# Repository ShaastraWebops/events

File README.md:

Offline Events - ERP
======

An app for events to use for general ERP usage

### Setup
1. Copy the `settings.sample.py` to `settings.py`
 - Edit the proxy settings if you are in a proxy environment. If not, comment those lines.
2. Copy the `client_secret.sample.json` to `client_secret.json`
 - Use your own secret key for google app.

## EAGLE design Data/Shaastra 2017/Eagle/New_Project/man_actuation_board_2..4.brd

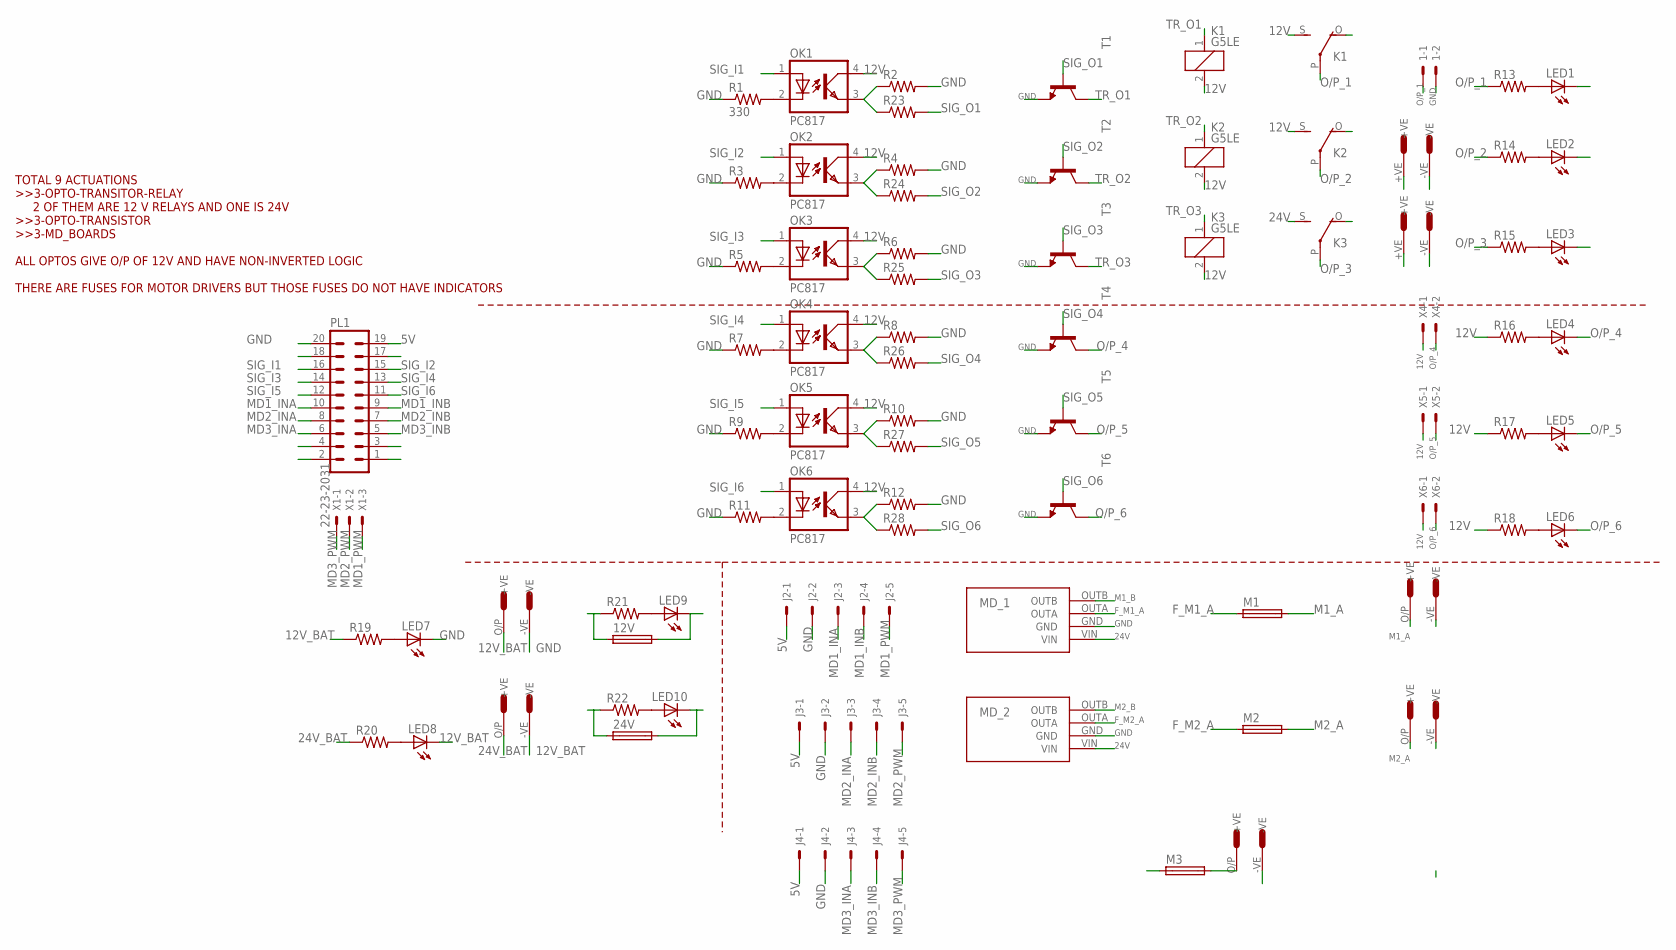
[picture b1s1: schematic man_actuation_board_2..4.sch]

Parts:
0-12_BAT, 12-24_I/P: MOLEX_4; MOLEX_2K14
1: 1; 22-23-2021
12V, 24V: SH25
J2, J3, J4: 22-27-2051-05; 6410-05
K1, K2, K3: G5LE
LED1, LED2, LED3, LED4, LED5, LED6, LED7, LED8, LED9, LED10: LED1206; LED-1206
M1, M2, M3: SH25
MD_1, MD_2: MOTOR_DRIVER
OK1, OK2, OK3, OK4, OK5, OK6: PC817; DIL04
PL1: ML20ML20; ML20
R1: 330; 1206
R2, R3, R4, R5, R6, R7, R8, R9, R10, R11, R12, R13, R14, R15, R16, R17, R18, R19, R20, R21, R22, R23, R24, R25, R26, R27, R28: RESISTOR1206; 1206
T1, T2, T3, T4, T5, T6: -NPN-TO5; TO5
U$1, U$2, U$3: MOLEX_4; MOLEX_2K14
U$4, U$5: MOLEXM; MOLEX_2K13
X1: 22-23-2031
X4: 4; 22-23-2021
X5: 5; 22-23-2021
X6: 6; 22-23-2021

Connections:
5V: J2.1, J3.1, J4.1, PL1.19
12V: 12V.2, K1.2, K1.S, K2.2, K2.S, K3.2, LED9.C, OK1.4 (COL), OK2.4 (COL), OK3.4 (COL), OK4.4 (COL), OK5.4 (COL), OK6.4 (COL), R16.1, R17.1, R18.1, X4.1, X5.1, X6.1
12V_BAT: 0-12_BAT.O/P (+VE), 12-24_I/P.-VE, 12V.1, LED8.C, R19.1, R21.1
12V_M: M3.2, U$3.O/P (+VE)
24V: 24V.2, K3.S, LED10.C, M3.1, MD_1.VIN, MD_2.VIN
24V_BAT: 12-24_I/P.O/P (+VE), 24V.1, R20.1, R22.1
F_M1_A: M1.1, MD_1.OUTA
F_M2_A: M2.1, MD_2.OUTA
GND: 0-12_BAT.-VE, 1.2, J2.2, J3.2, J4.2, LED1.C, LED2.C, LED3.C, LED7.C, MD_1.GND, MD_2.GND, PL1.20, R1.1, R2.2, R3.1, R4.2, R5.1, R6.2, R7.1, R8.2, R9.1, R10.2, R11.1, R12.2, T1.1 (E), T2.1 (E), T3.1 (E), T4.1 (E), T5.1 (E), T6.1 (E), U$3.-VE, U$4.-VE, U$5.-VE
M1_A: M1.2, U$1.O/P (+VE)
M1_B: MD_1.OUTB, U$1.-VE
M2_A: M2.2, U$2.O/P (+VE)
M2_B: MD_2.OUTB, U$2.-VE
MD1_INA: J2.3, PL1.10
MD1_INB: J2.4, PL1.9
MD1_PWM: J2.5, X1.3
MD2_INA: J3.3, PL1.8
MD2_INB: J3.4, PL1.7
MD2_PWM: J3.5, X1.2
MD3_INA: J4.3, PL1.6
MD3_INB: J4.4, PL1.5
MD3_PWM: J4.5, X1.1
unnamed: OK1.2 (C), R1.2
unnamed: LED1.A, R13.2
unnamed: LED2.A, R14.2
unnamed: OK2.2 (C), R3.2
unnamed: LED3.A, R15.2
unnamed: LED4.A, R16.2
unnamed: LED5.A, R17.2
unnamed: LED6.A, R18.2
unnamed: LED7.A, R19.2
unnamed: OK3.2 (C), R5.2
unnamed: LED8.A, R20.2
unnamed: OK4.2 (C), R7.2
unnamed: LED9.A, R21.2
unnamed: LED10.A, R22.2
unnamed: OK5.2 (C), R9.2
unnamed: OK1.3 (EMIT), R2.1, R23.1
unnamed: OK2.3 (EMIT), R4.1, R24.1
unnamed: OK3.3 (EMIT), R6.1, R25.1
unnamed: OK4.3 (EMIT), R8.1, R26.1
unnamed: OK5.3 (EMIT), R10.1, R27.1
unnamed: OK6.3 (EMIT), R12.1, R28.1
unnamed: OK6.2 (C), R11.2
O/P_1: 1.1, K1.P, R13.1
O/P_2: K2.P, R14.1, U$5.+VE
O/P_3: K3.P, R15.1, U$4.+VE
O/P_4: LED4.C, T4.3 (C), X4.2
O/P_5: LED5.C, T5.3 (C), X5.2
O/P_6: LED6.C, T6.3 (C), X6.2
SIG_I1: OK1.1 (A), PL1.16
SIG_I2: OK2.1 (A), PL1.15
SIG_I3: OK3.1 (A), PL1.14
SIG_I4: OK4.1 (A), PL1.13
SIG_I5: OK5.1 (A), PL1.12
SIG_I6: OK6.1 (A), PL1.11
SIG_O1: R23.2, T1.2 (B)
SIG_O2: R24.2, T2.2 (B)
SIG_O3: R25.2, T3.2 (B)
SIG_O4: R26.2, T4.2 (B)
SIG_O5: R27.2, T5.2 (B)
SIG_O6: R28.2, T6.2 (B)
TR_O1: K1.1, T1.3 (C)
TR_O2: K2.1, T2.3 (C)
TR_O3: K3.1, T3.3 (C)

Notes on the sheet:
TOTAL 9 ACTUATIONS >>3-OPTO-TRANSITOR-RELAY 2 OF THEM ARE 12 V RELAYS AND ONE IS 24V >>3-OPTO-TRANSISTOR >>3-MD_BOARDS ALL OPTOS GIVE O/P OF 12V AND HAVE NON-INVERTED LOGIC THERE ARE FUSES FOR MOTOR DRIVERS BUT THOSE FUSES DO NOT HAVE INDICATORS

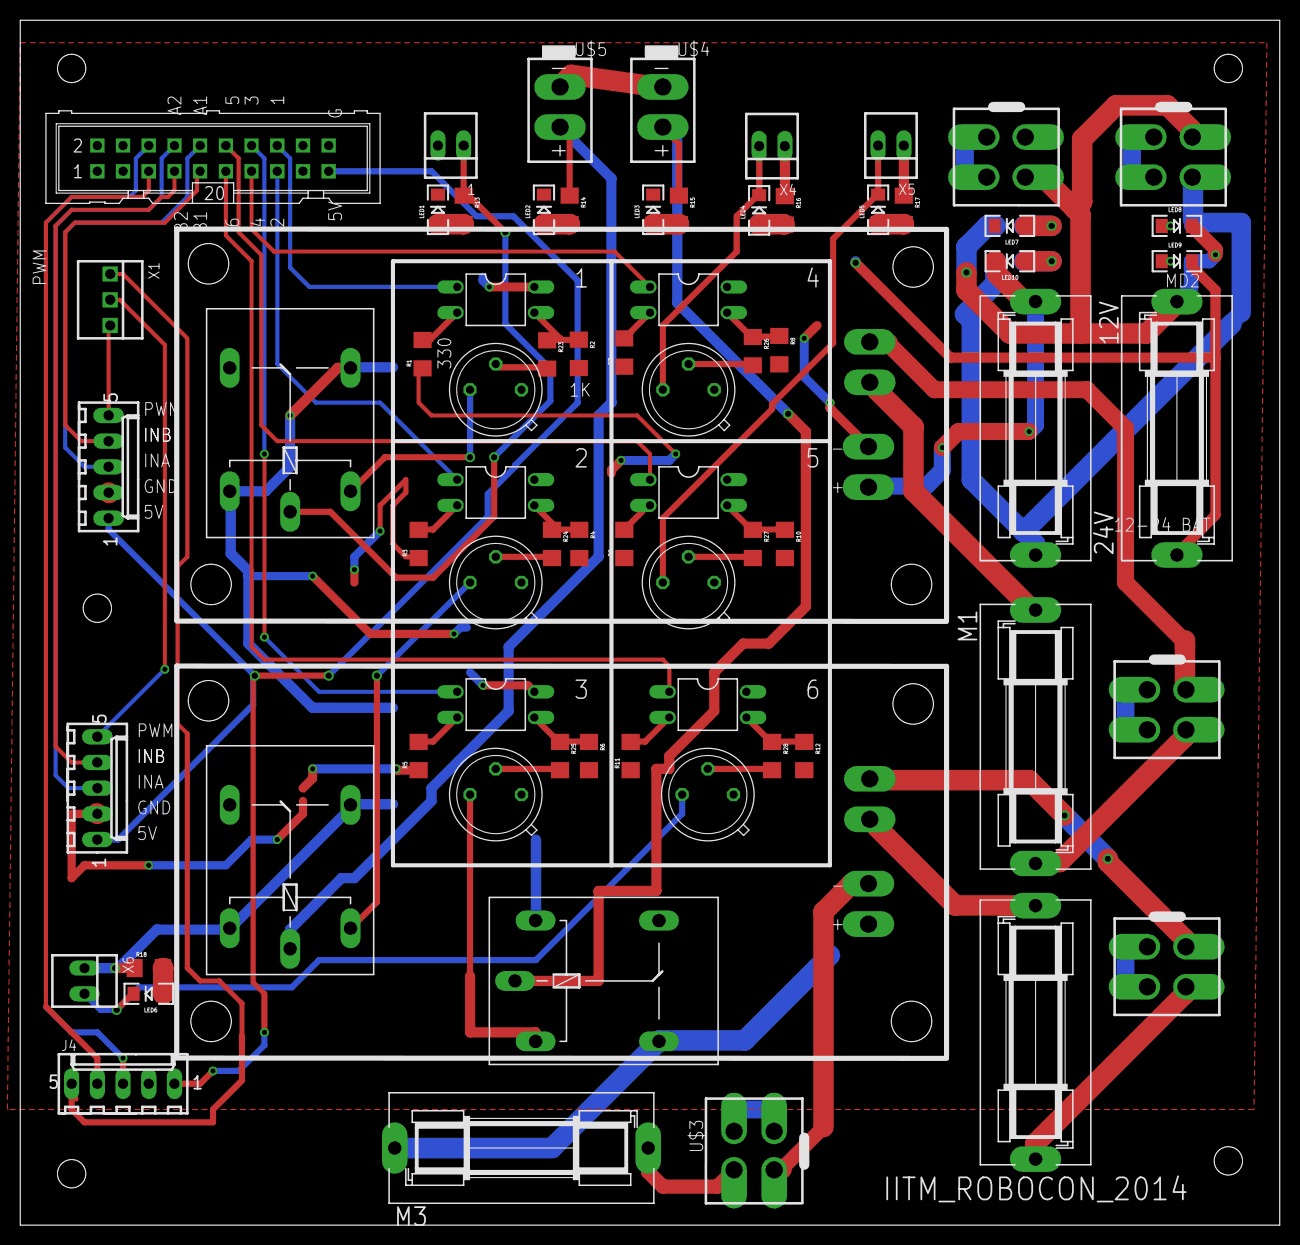
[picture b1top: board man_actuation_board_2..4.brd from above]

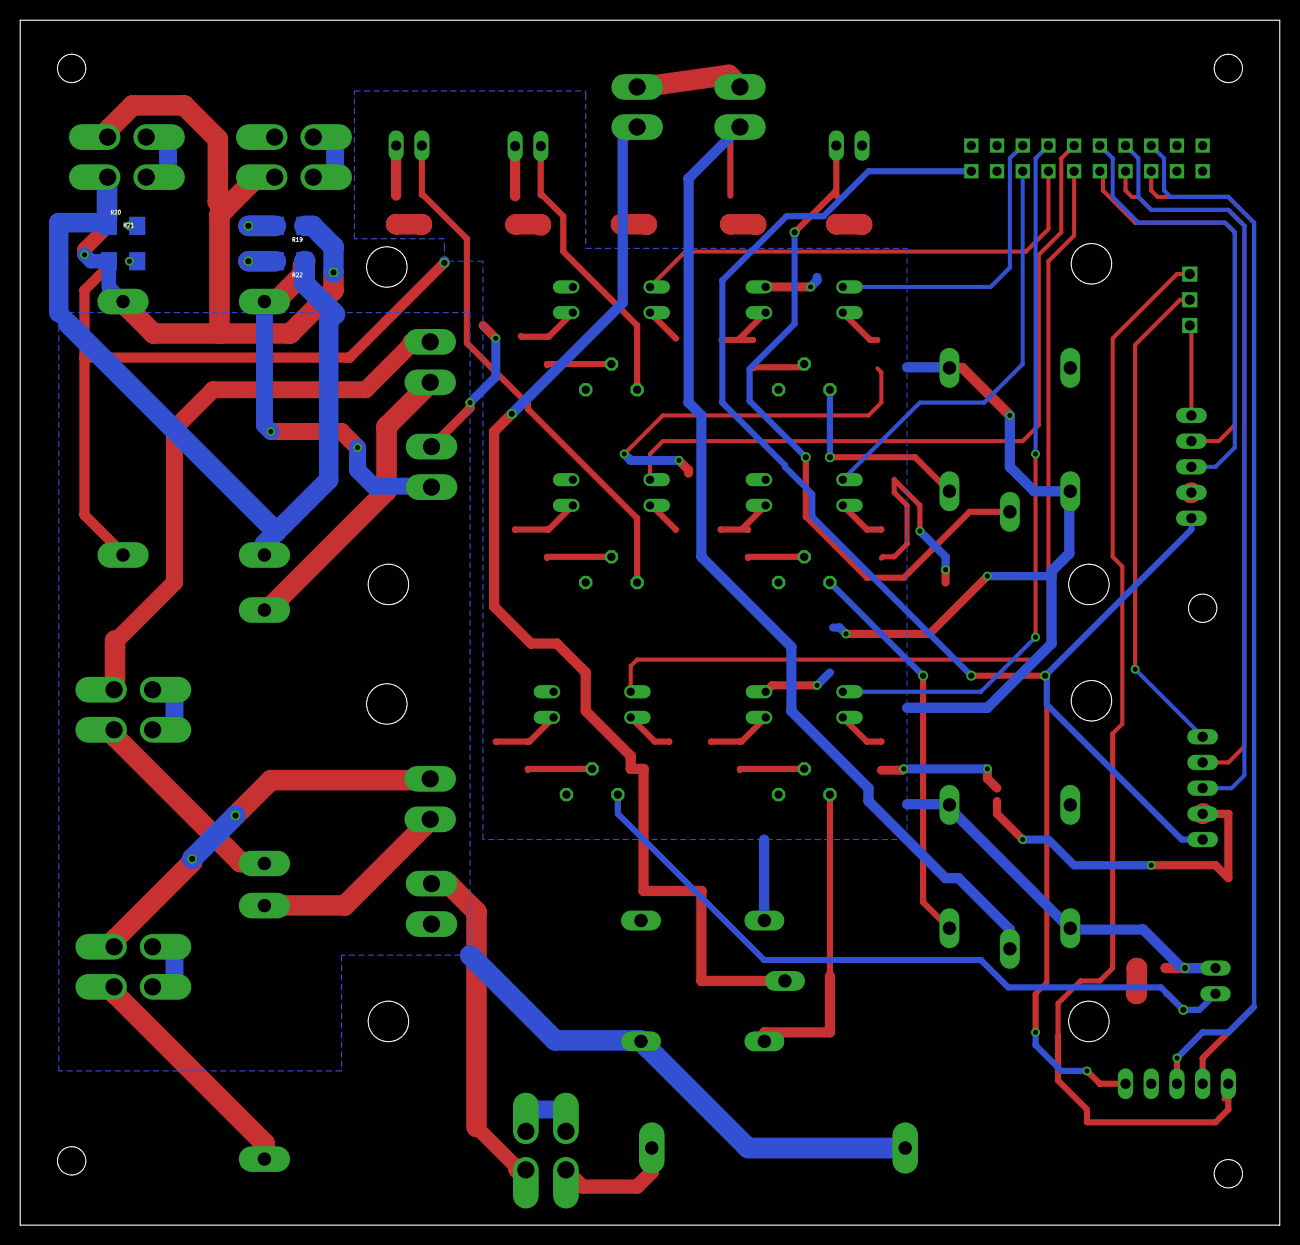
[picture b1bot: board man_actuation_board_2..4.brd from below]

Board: 2 copper layers, 124.5 x 119.1 mm, 76 parts (4 on the bottom side), 65 nets.

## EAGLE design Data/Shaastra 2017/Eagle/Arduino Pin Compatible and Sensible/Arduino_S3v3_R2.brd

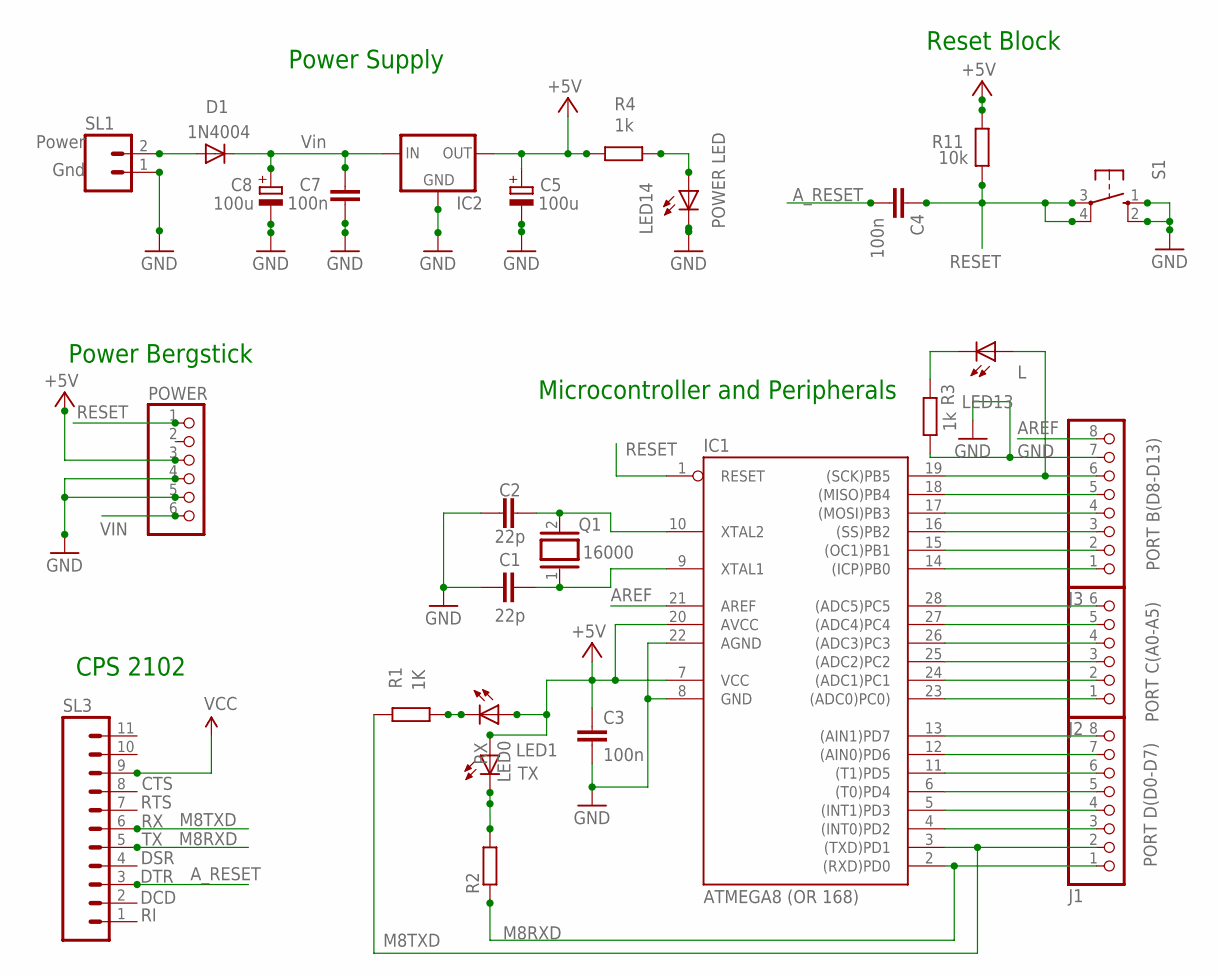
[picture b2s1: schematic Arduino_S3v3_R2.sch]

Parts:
C1, C2: 22p; C050-025X075
C3, C4, C7: 100n; C050-025X075
C5, C8: 100u; E3,5-8
D1: 1N4004; DO41-10
IC1: ATMEGA8 (OR 168); DIL28-3
IC2: 78XXL
J1: PORT D(D0-D7); 1X08
J2: PORT C(A0-A5); 1X06
J3: PORT B(D8-D13); 1X08
LED0: RX; LED3MM
LED1: TX; LED3MM
LED13: L; LED3MM
LED14: POWER LED; LED3MM
POWER: PINHD-1X6; 1X06
Q1: 16000; Q
R1: 1K; 0207/10
R2: R-EU_0207/10; 0207/10
R3, R4: 1k; 0207/10
R11: 10k; 0207/10
S1: 10-XX; B3F-10XX
SL1: M02; 02P
SL3: M11; 11P

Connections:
3V3: POWER.2
+5V: C3.1, C5.+, IC1.7 (VCC), IC1.20 (AVCC), IC2.OUT, LED0.A, LED1.A, POWER.3, R4.2, R11.2
AREF: IC1.21 (AREF), J3.8
AUTO_RESET: C4.2, SL3.3
GND: C1.1, C2.1, C3.2, C5.-, C7.1, C8.-, IC1.8 (GND), IC1.22 (AGND), IC2.GND, J3.7, LED14.K (C), POWER.4, POWER.5, R3.1, S1.1 (S), S1.2 (S1), SL1.1
M8RXD: IC1.2 ((RXD)PD0), J1.1, R2.1, SL3.5
M8TXD: IC1.3 ((TXD)PD1), J1.2, R1.2, SL3.6
unnamed: IC1.18 ((MISO)PB4), J3.5
unnamed: LED0.K (C), R1.1
unnamed: LED14.A, R4.1
unnamed: IC1.17 ((MOSI)PB3), J3.4
unnamed: IC1.14 ((ICP)PB0), J3.1
unnamed: C1.2, IC1.9 (XTAL1), Q1.1
unnamed: C2.2, IC1.10 (XTAL2), Q1.2
unnamed: LED1.K (C), R2.2
unnamed: IC1.4 ((INT0)PD2), J1.3
unnamed: IC1.5 ((INT1)PD3), J1.4
unnamed: IC1.6 ((T0)PD4), J1.5
unnamed: IC1.11 ((T1)PD5), J1.6
unnamed: IC1.12 ((AIN0)PD6), J1.7
unnamed: IC1.13 ((AIN1)PD7), J1.8
unnamed: IC1.23 ((ADC0)PC0)), J2.1
unnamed: IC1.24 ((ADC1)PC1), J2.2
unnamed: IC1.25 ((ADC2)PC2), J2.3
unnamed: IC1.26 ((ADC3)PC3), J2.4
unnamed: IC1.27 ((ADC4)PC4), J2.5
unnamed: IC1.28 ((ADC5)PC5), J2.6
unnamed: IC1.15 ((OC1)PB1), J3.2
unnamed: IC1.16 ((SS)PB2), J3.3
unnamed: LED13.K (C), R3.2
POWER: D1.A, SL1.2
RESET: C4.1, IC1.1 (RESET), POWER.1, R11.1, S1.3, S1.4 (P1)
SCK: IC1.19 ((SCK)PB5), J3.6, LED13.A
VCC: SL3.9
VIN: C7.2, C8.+, D1.C, IC2.IN, POWER.6

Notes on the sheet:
Vin
Gnd
Power Supply
Reset Block
Power Bergstick
CPS 2102
Microcontroller and Peripherals
CTS
RTS
DSR
DTR
DCD
A_RESET
Power

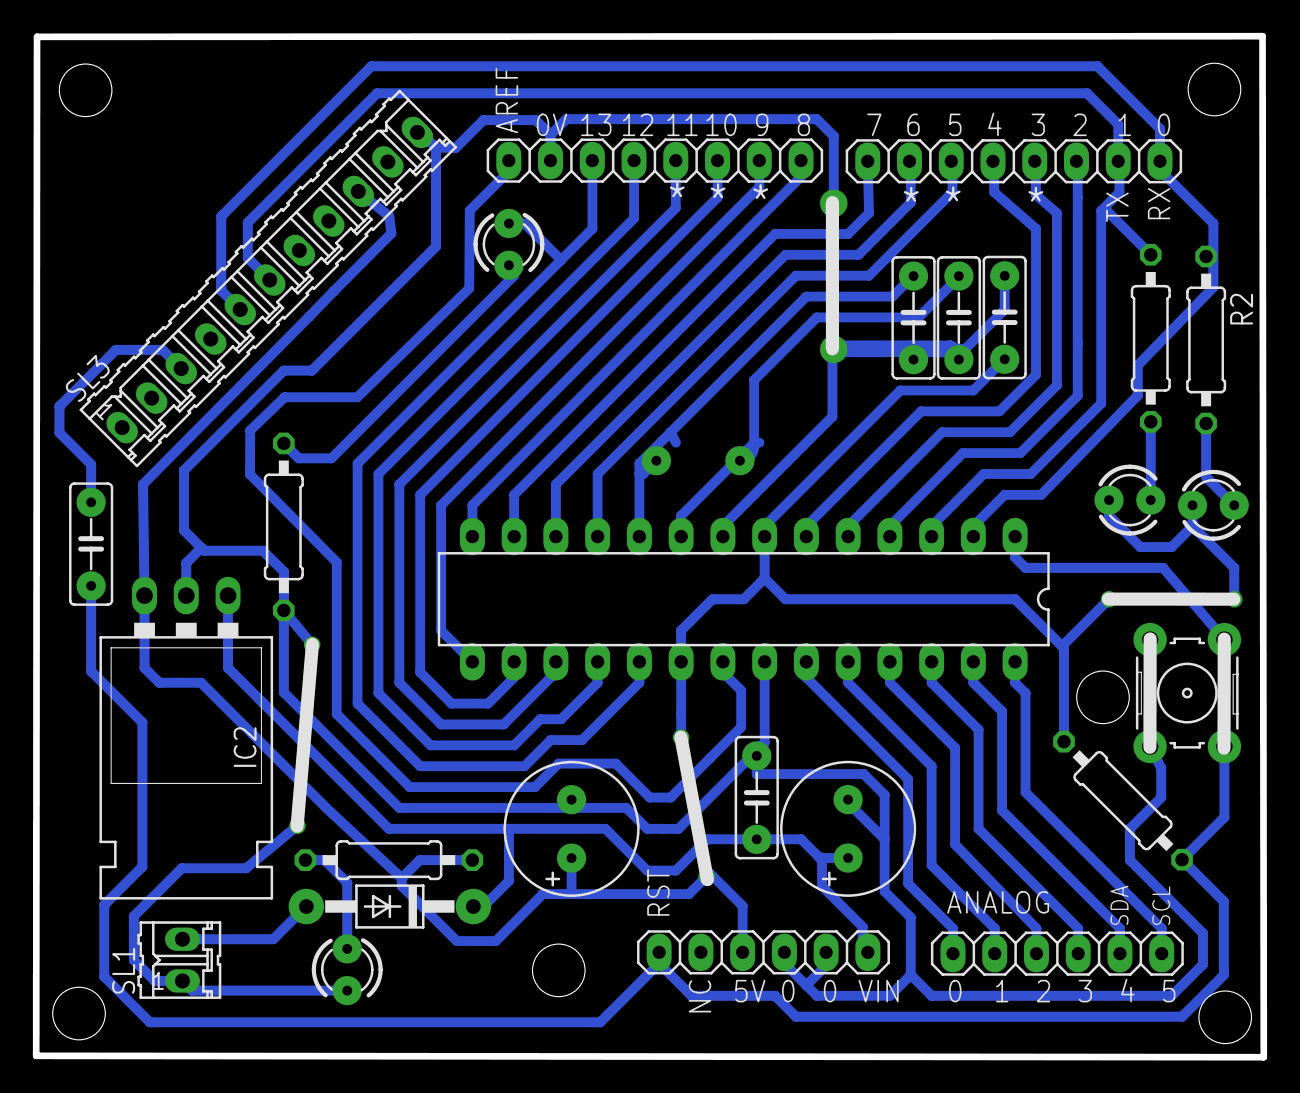
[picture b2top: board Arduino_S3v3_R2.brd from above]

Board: 2 copper layers, 74.7 x 62.1 mm, 27 parts (1 on the bottom side), 33 nets.

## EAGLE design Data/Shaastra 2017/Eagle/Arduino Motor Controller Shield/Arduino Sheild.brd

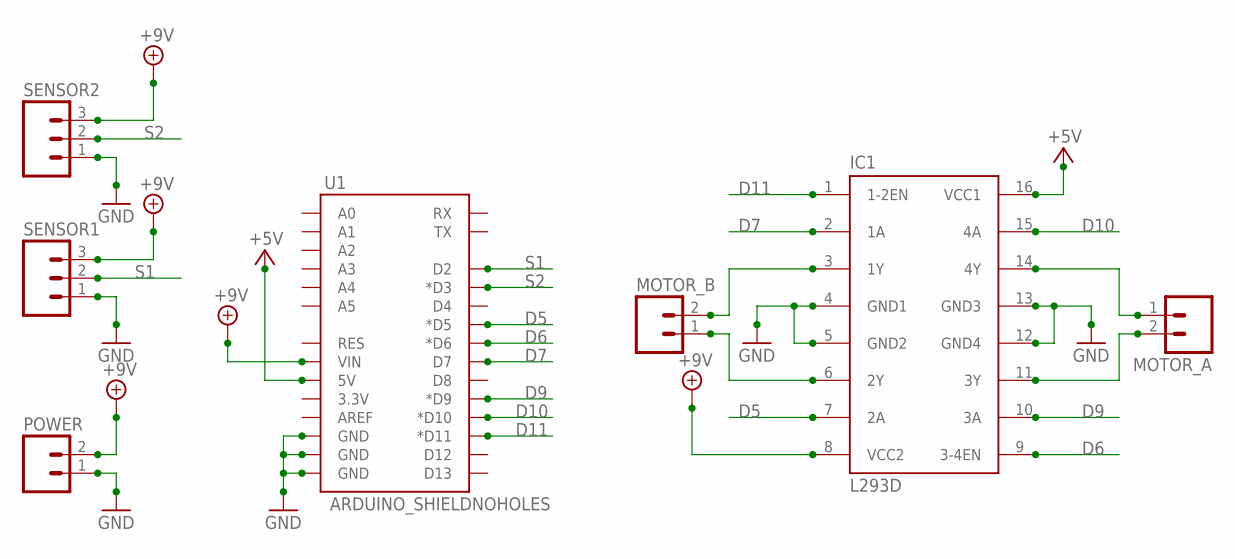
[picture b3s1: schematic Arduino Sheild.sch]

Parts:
IC1: L293D; DIL16
MOTOR_A: M02; 02P
MOTOR_B: M02; 02P
POWER: M02; 02P
SENSOR1, SENSOR2: M03; 03P
U1: ARDUINO_SHIELDNOHOLES; DUEMILANOVE_SHIELD_NOHOLES

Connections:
+5V: IC1.16 (VCC1), U1.5V
+9V: IC1.8 (VCC2), POWER.2, SENSOR1.3, SENSOR2.3, U1.VIN
D5: IC1.7 (2A), U1.D5 (*D5)
D6: IC1.9 (3-4EN), U1.D6 (*D6)
D7: IC1.2 (1A), U1.D7
D9: IC1.10 (3A), U1.D9 (*D9)
D10: IC1.15 (4A), U1.D10 (*D10)
D11: IC1.1 (1-2EN), U1.D11 (*D11)
GND: IC1.4 (GND1), IC1.5 (GND2), IC1.12 (GND4), IC1.13 (GND3), POWER.1, SENSOR1.1, SENSOR2.1, U1.GND@0 (GND), U1.GND@1 (GND), U1.GND@2 (GND)
unnamed: IC1.3 (1Y), MOTOR_B.2
unnamed: IC1.6 (2Y), MOTOR_B.1
unnamed: IC1.14 (4Y), MOTOR_A.1
unnamed: IC1.11 (3Y), MOTOR_A.2
S1: SENSOR1.2, U1.D2
S2: SENSOR2.2, U1.D3 (*D3)

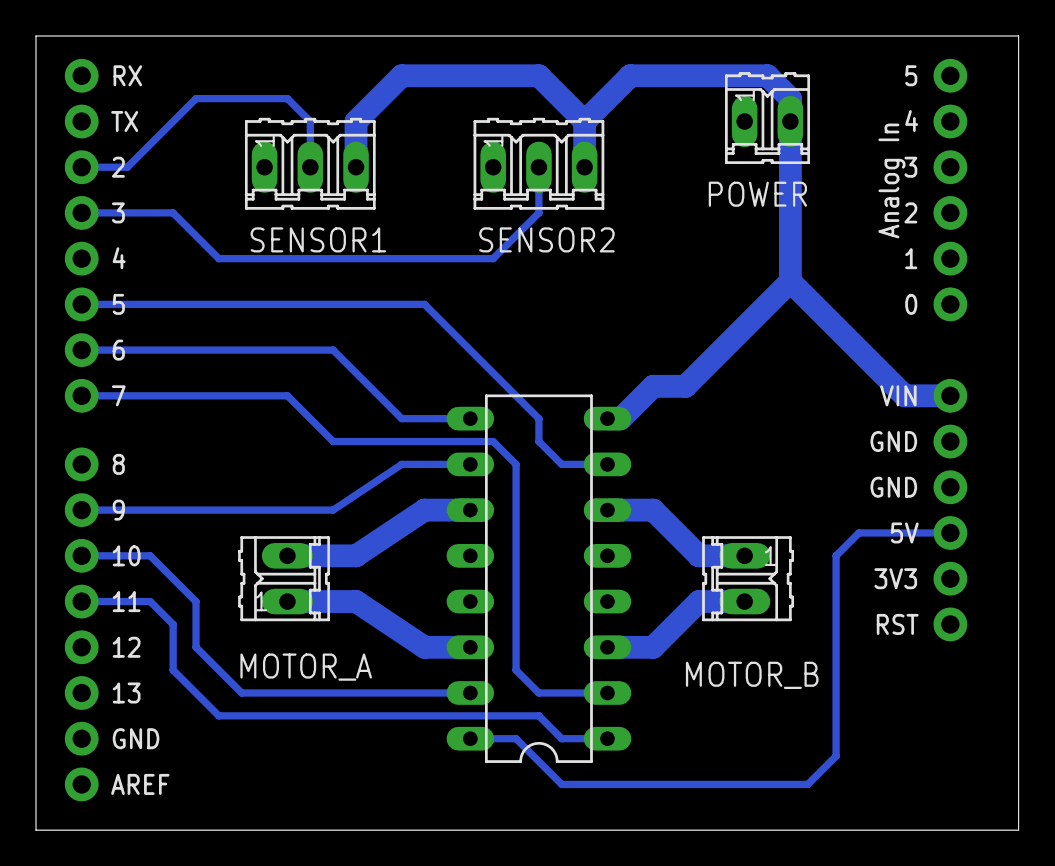
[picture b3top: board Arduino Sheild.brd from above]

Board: 2 copper layers, 54.6 x 44.1 mm, 7 parts (0 on the bottom side), 15 nets.

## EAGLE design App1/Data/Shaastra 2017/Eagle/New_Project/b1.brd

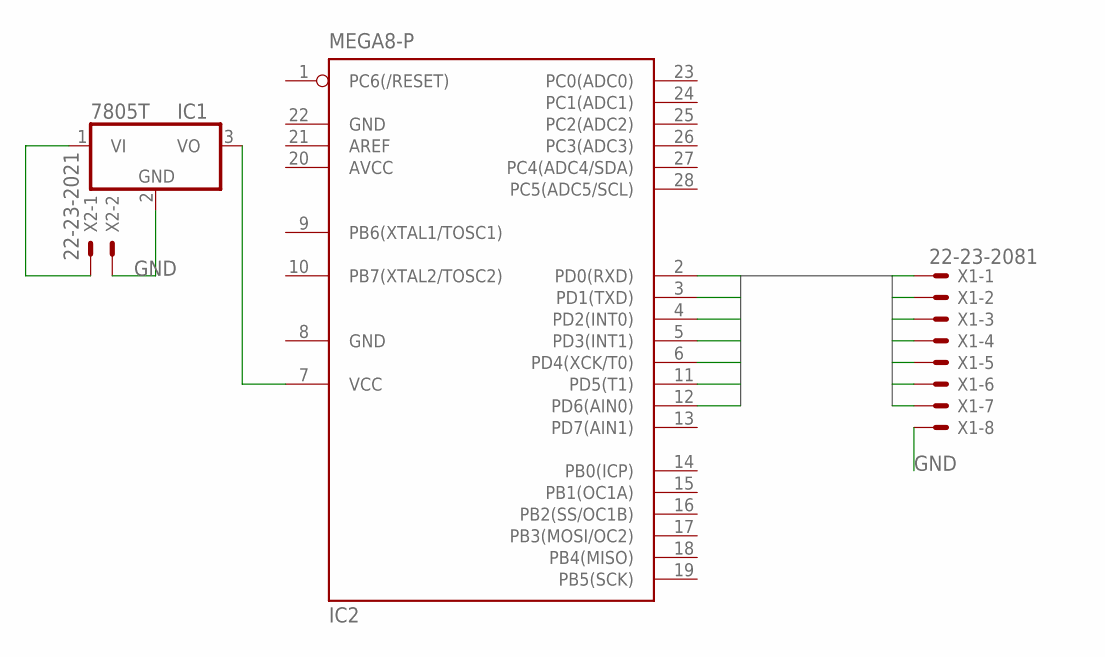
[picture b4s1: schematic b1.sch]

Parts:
IC1: 7805T; TO220H
IC2: MEGA8-P; DIL28-3
X1: 22-23-2081
X2: 22-23-2021

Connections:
AVCC: IC2.20 (AVCC)
GND: IC1.2 (GND), IC2.8 (GND), IC2.22 (GND), X1.8, X2.2
unnamed: IC1.1 (VI), X2.1
unnamed: IC1.3 (VO), IC2.7 (VCC)
P1: IC2.2 (PD0(RXD)), X1.1
P2: IC2.3 (PD1(TXD)), X1.2
P3: IC2.4 (PD2(INT0)), X1.3
P4: IC2.5 (PD3(INT1)), X1.4
P5: IC2.6 (PD4(XCK/T0)), X1.5
P6: IC2.11 (PD5(T1)), X1.6
P7: IC2.12 (PD6(AIN0)), X1.7

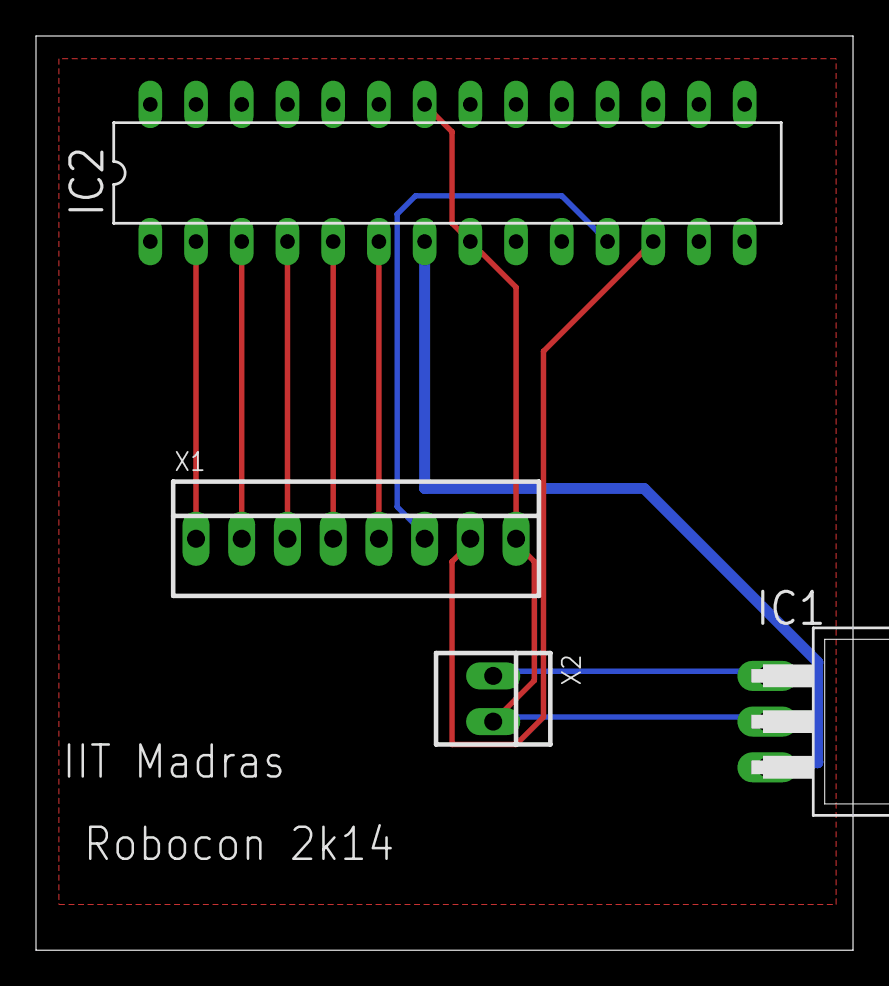
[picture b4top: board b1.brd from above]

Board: 2 copper layers, 45.4 x 50.8 mm, 4 parts (0 on the bottom side), 10 nets.

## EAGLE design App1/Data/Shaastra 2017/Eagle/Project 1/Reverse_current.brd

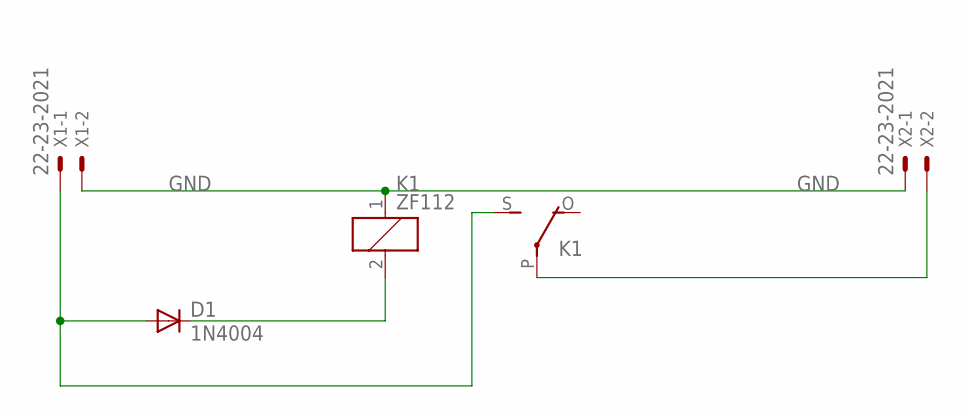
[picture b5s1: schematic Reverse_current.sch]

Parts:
D1: 1N4004; DO41-10
K1: ZF112
X1, X2: 22-23-2021

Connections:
GND: K1.1, X1.2, X2.1
unnamed: D1.A, K1.S, X1.1
unnamed: D1.C, K1.2
unnamed: K1.P, X2.2

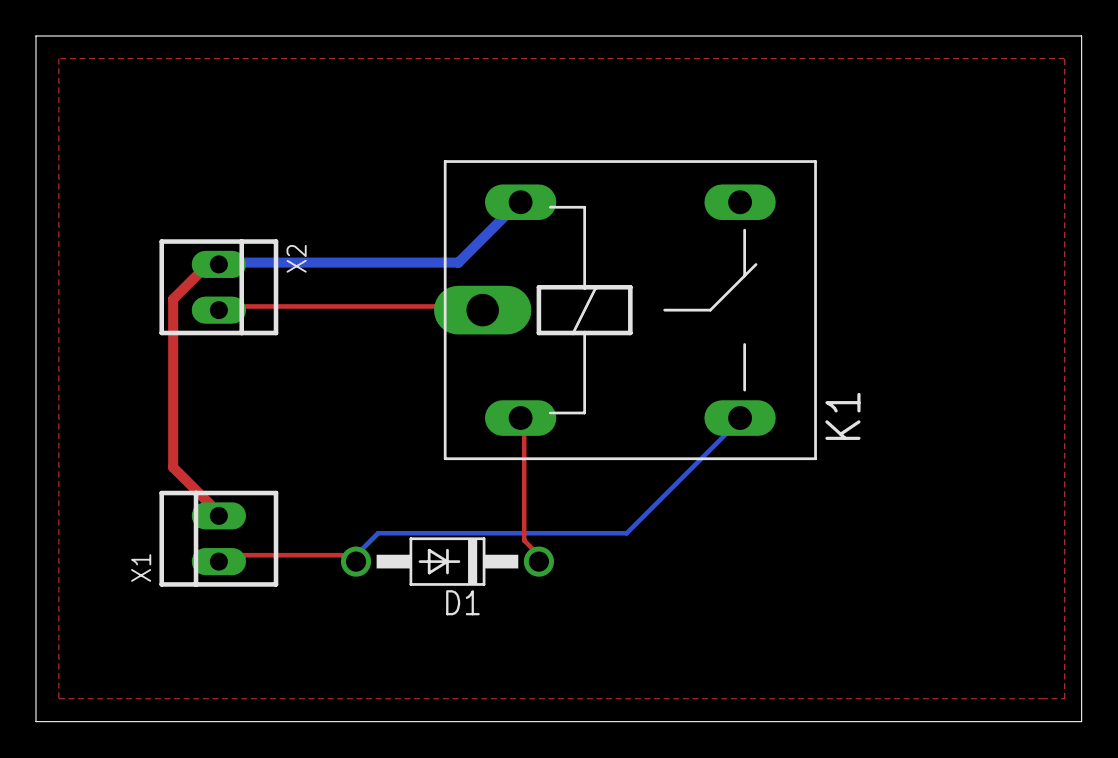
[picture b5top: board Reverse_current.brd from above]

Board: 2 copper layers, 58.1 x 38.1 mm, 4 parts (0 on the bottom side), 4 nets.

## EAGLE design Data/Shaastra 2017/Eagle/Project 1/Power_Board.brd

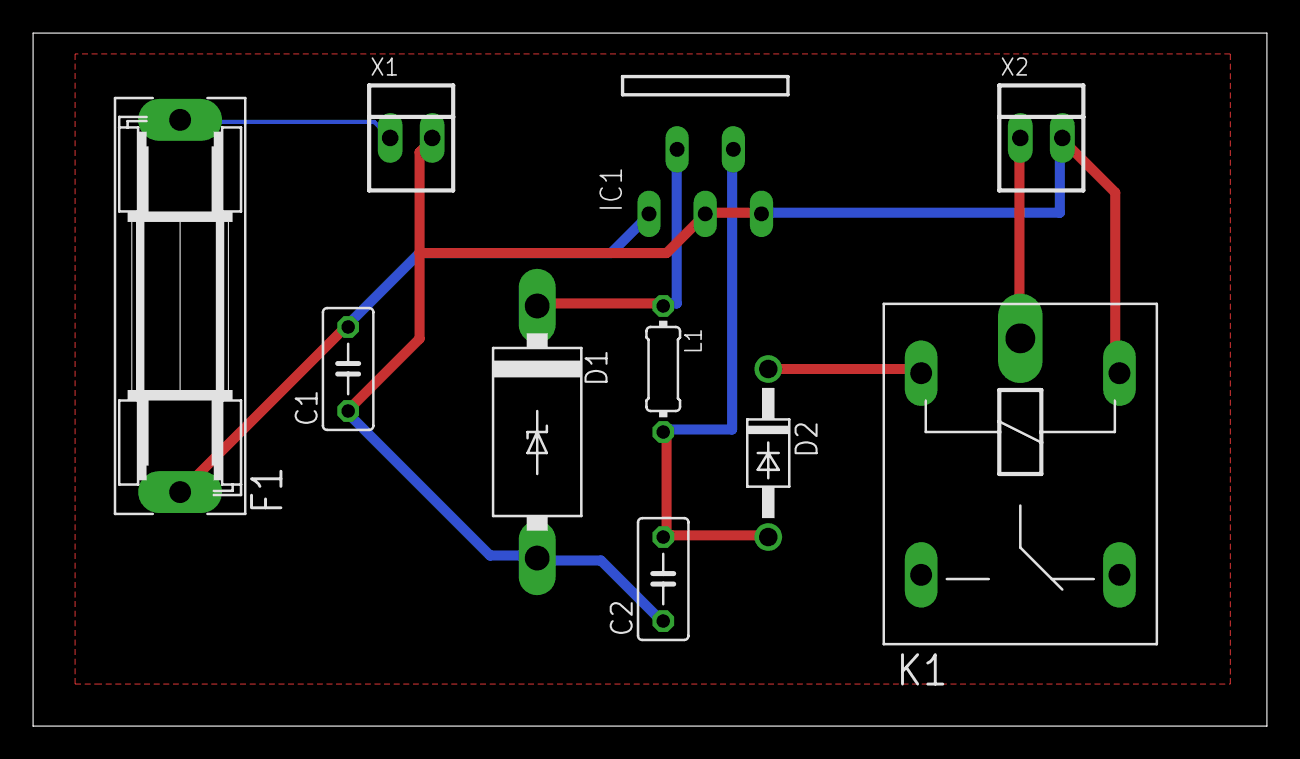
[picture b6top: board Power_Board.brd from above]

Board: 2 copper layers, 74.6 x 41.9 mm, 10 parts (0 on the bottom side), 7 nets.

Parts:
C1: 100 microF; C050-030X075
C2: 1000microF; C050-030X075
D1: 1N5908; C4111-15
D2: 1N4004; DO41-10
F1: FUSESH22,5; SH22,5
IC1: LM2576T; TO220-5
K1: ZF112
L1: 100 microH; 0204/7
X1, X2: 22-23-2021

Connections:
GND: C1.1, C2.1, D1.A, IC1.3, IC1.5, K1.1, X1.2, X2.2
unnamed: K1.P, X2.1
unnamed: D2.C, K1.2
unnamed: D1.C, IC1.2, L1.1
unnamed: C2.2, D2.A, IC1.4, L1.2
unnamed: F1.2, X1.1
VIN: C1.2, F1.1, IC1.1

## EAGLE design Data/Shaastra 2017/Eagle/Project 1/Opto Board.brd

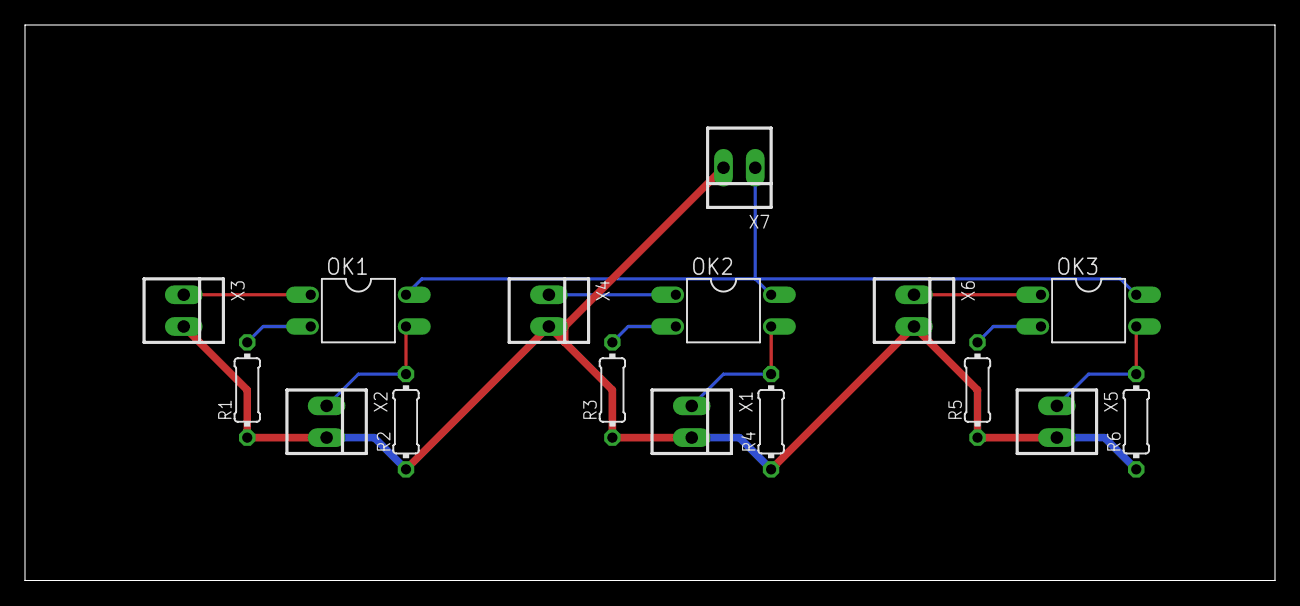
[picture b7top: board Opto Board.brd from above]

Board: 2 copper layers, 100.0 x 44.4 mm, 16 parts (0 on the bottom side), 11 nets.

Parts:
OK1, OK2, OK3: LTV816; DIL04
R1, R3, R5: 1000; 0204/7
R2, R4, R6: 5000; 0204/7
X1, X2, X3, X4, X5, X6, X7: 22-23-2021

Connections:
GND: R1.1, R2.1, R3.1, R4.1, R5.1, R6.1, X1.2, X2.2, X3.2, X4.2, X5.2, X6.2, X7.2
unnamed: OK1.1, X3.1
unnamed: OK1.2, R1.2
unnamed: OK2.1, X4.1
unnamed: OK3.1, X6.1
unnamed: OK2.2, R3.2
unnamed: OK1.3, R2.2, X2.1
unnamed: OK3.2, R5.2
unnamed: OK2.3, R4.2, X1.1
unnamed: OK3.3, R6.2, X5.1
unnamed: OK1.4, OK2.4, OK3.4, X7.1

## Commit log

2014-06-18 something
2014-06-21 tried browser less login.. not possible yet.. with browser only once a login is required
2014-06-21 reads complete file list in drive and saves it for further processing
2014-06-22 quick file list download, GUI develop v1.0
2014-06-30 prelim sync
2014-06-30 Major revamp
2014-06-30 Readded deleted files

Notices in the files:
parts and their libraries:
SparkFun-Boards: Licensing: CC v3.0 Share-Alike You are welcome to use this library for commercial purposes.
